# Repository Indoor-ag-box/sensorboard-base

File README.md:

[Indoor Agriculture Project](https://docs.google.com/document/d/1ArcZqPgIa82AwvjWtvZ9FeCffs26SfxBspnVomPGeAw/edit#)

## Sensorboard

The Sensorboard is based off of the [Arduino Nano](https://store.arduino.cc/usa/arduino-nano). It has a very minimal UI to:

* Enable and disable sensors on the board

* Select the ID number for the board

* Display current sensor readings

* Calibrate sensors (Calibration factors are stored in EEPROM)

The UI is based on an:

* [8x2 Char LCD Module](https://www.digikey.com/product-detail/en/newhaven-display-intl/NHD-0208BZ-FL-YBW/NHD-0208BZ-FL-YBW-ND/1701135)

* 3 Pushbuttons

The sensorboard reports all RAW values back to the pi. These may be filtered and averaged etc, but conversion from VOLTAGE to the actual data is handled by the pi.

The connections are as follows:

### Arduino Pins

<table>
  <tr>
    <td>Pin Name</td>
    <td>Pin Function</td>
    <td>Short Name</td>
    <td>Location</td>
  </tr>
  <tr>
    <td>D2 (INT)</td>
    <td>Misc Digital Input</td>
    <td>EMDI0</td>
    <td>Screw Terminal</td>
  </tr>
  <tr>
    <td>D3
</td>
    <td>Shift Register Serial</td>
    <td>SREG_SER</td>
    <td>On Board
</td>
  </tr>
  <tr>
    <td>D4</td>
    <td>Shift Register SRCLK</td>
    <td>SREG_SRCLK</td>
    <td>On Board</td>
  </tr>
  <tr>
    <td>D5</td>
    <td>CO2 Sensor UART TX</td>
    <td>ECO2R</td>
    <td>Board Connector</td>
  </tr>
  <tr>
    <td>D6</td>
    <td>CO2 Sensor UART RX</td>
    <td>ECO2R</td>
    <td>Board Connector</td>
  </tr>
  <tr>
    <td>D7 (SDA)</td>
    <td>RGB Color Sensor I2C SDA</td>
    <td>ECSDA</td>
    <td>Board Connector</td>
  </tr>
  <tr>
    <td>D8 (SCL)</td>
    <td>RGB Color Sensor I2C SCL</td>
    <td>ECSCL</td>
    <td>Board Connector</td>
  </tr>
  <tr>
    <td>D9</td>
    <td>Load Sensor Data</td>
    <td>LSDAT</td>
    <td>On Board</td>
  </tr>
  <tr>
    <td>D10</td>
    <td>Load Sensor Clock</td>
    <td>LSCLK</td>
    <td>On Board</td>
  </tr>
  <tr>
    <td>D11 (PWM)</td>
    <td>LCD Backlight LED+</td>
    <td>OLED+</td>
    <td>On Board</td>
  </tr>
  <tr>
    <td>D12</td>
    <td>Shift Register RCLK</td>
    <td>SREG_RCLK</td>
    <td>On Board</td>
  </tr>
  <tr>
    <td>D13</td>
    <td>Voltage Divider Enable</td>
    <td>DIVEN</td>
    <td>On Board</td>
  </tr>
  <tr>
    <td>A0</td>
    <td>Mux Sig Pin</td>
    <td>MUX_SIG</td>
    <td>On Board</td>
  </tr>
  <tr>
    <td>A1</td>
    <td>Mux S0</td>
    <td>MUX_S0</td>
    <td>On Board</td>
  </tr>
  <tr>
    <td>A2</td>
    <td>Mux S1</td>
    <td>MUX_S1</td>
    <td>On Board</td>
  </tr>
  <tr>
    <td>A3</td>
    <td>Mux S2</td>
    <td>MUX_S2</td>
    <td>On Board</td>
  </tr>
  <tr>
    <td>A4</td>
    <td>Hardware I2C SDA (For External Comms)</td>
    <td>I2C_SDA</td>
    <td>Board Connector</td>
  </tr>
  <tr>
    <td>A5</td>
    <td>Hardware I2C SCL (For External Comms)</td>
    <td>I2C_SDL</td>
    <td>Board Connector</td>
  </tr>
  <tr>
    <td>A6</td>
    <td>Mux S3</td>
    <td>MUX_S3</td>
    <td>On Board</td>
  </tr>
  <tr>
    <td>A7</td>
    <td>Mux EN</td>
    <td>MUX_EN</td>
    <td>On Board</td>
  </tr>
</table>

### Multiplexer

<table>
  <tr>
    <td>Pin Name</td>
    <td>Pin Function</td>
    <td>Short Name</td>
    <td>Location</td>
  </tr>
  <tr>
    <td>I0</td>
    <td>External Temp Sensor 0</td>
    <td>ETMP0</td>
    <td>Screw Terminal</td>
  </tr>
  <tr>
    <td>I1</td>
    <td>External Temp Sensor 1</td>
    <td>ETMP1</td>
    <td>Screw Terminal</td>
  </tr>
  <tr>
    <td>I2</td>
    <td>External Temp Sensor 2</td>
    <td>ETMP2</td>
    <td>Screw Terminal</td>
  </tr>
  <tr>
    <td>I3</td>
    <td>Soil Moisture Sensor 1 </td>
    <td>ESMT0</td>
    <td>Screw Terminal</td>
  </tr>
  <tr>
    <td>I4</td>
    <td>Soil Moisture Sensor 2</td>
    <td>ESMT0</td>
    <td>Screw Terminal</td>
  </tr>
  <tr>
    <td>I5</td>
    <td>Onboard Temp Sensor 0</td>
    <td>OTMP0</td>
    <td>On Board</td>
  </tr>
  <tr>
    <td>I6</td>
    <td>Onboard LDR 0</td>
    <td>OLDR0</td>
    <td>Board Connector</td>
  </tr>
  <tr>
    <td>I7</td>
    <td>O2 Sensor</td>
    <td>BO2G0</td>
    <td>On Board</td>
  </tr>
  <tr>
    <td>I8</td>
    <td>Ambient Humidity</td>
    <td>OMST0</td>
    <td>On board</td>
  </tr>
  <tr>
    <td>I9</td>
    <td>External Turbidity 0</td>
    <td>ETRB0</td>
    <td>Board Connector</td>
  </tr>
  <tr>
    <td>I10</td>
    <td></td>
    <td></td>
    <td></td>
  </tr>
  <tr>
    <td>I11</td>
    <td></td>
    <td></td>
    <td></td>
  </tr>
  <tr>
    <td>I12</td>
    <td>External Board Detection</td>
    <td>EEBD0</td>
    <td>Board Connector</td>
  </tr>
  <tr>
    <td>I13</td>
    <td>UI Button 1 (<)</td>
    <td>OUI0</td>
    <td>On Board</td>
  </tr>
  <tr>
    <td>I14</td>
    <td>UI Button 2 (*)</td>
    <td>OUI1</td>
    <td>On Board</td>
  </tr>
  <tr>
    <td>I15</td>
    <td>UI Button 3 (>)</td>
    <td>OUI2</td>
    <td>On Board</td>
  </tr>
</table>

A sensor board that we can stick all over the cabinet to sense critical environmental data. There will be more than one of these boards through the whole design. Sensor boards are based around the arduino mini which communicates with the Raspberry Pi as a master and the arduino responds as a [slave](https://www.arduino.cc/en/Tutorial/MasterWriter). 

Should be able to detect following variables (sensors are linked as hyperlinks):

* [Onboard temperature](https://www.digikey.com/product-detail/en/ametherm/1DC103K-EC/570-1229-ND/5970118)

* [External temperature (optional through some kind of screw terminal)](https://www.adafruit.com/product/372)

* [Ambient light Level](https://www.digikey.com/products/en?dc=16426)

* [Light Color](https://www.adafruit.com/product/1334?gclid=Cj0KCQiA2Y_UBRCGARIsALglqQ1tPgwjs8Q0iPb3CzkeynlRJk4hzR49dijqtHjcTRZPo-LJaD_BfX8aAv9AEALw_wcB)

* [Ambient Moisture](https://www.digikey.com/product-detail/en/honeywell-sensing-and-productivity-solutions/HIH-4030-003/480-3167-ND/1886072)

* [Soil Moisture (external)](https://www.sparkfun.com/products/13322)

* [O2 Content](https://www.seeedstudio.com/Grove-Oxygen-Sensor%28ME2-O2-%D0%A420%29-p-1541.html)

* [CO2 Content](https://www.ebay.com/itm/New-MH-Z19B-Infrared-Carbon-Dioxide-CO2-Monitor-Sensor-Module-UART-PWM-Output/302501791946?epid=5002546034&hash=item466e8308ca:g:nwoAAOSwH-dZ8ae~:sc:USPSFirstClass!02169!US!-1)

* [Reservoir Water Turgidity](https://www.dfrobot.com/product-1394.html)

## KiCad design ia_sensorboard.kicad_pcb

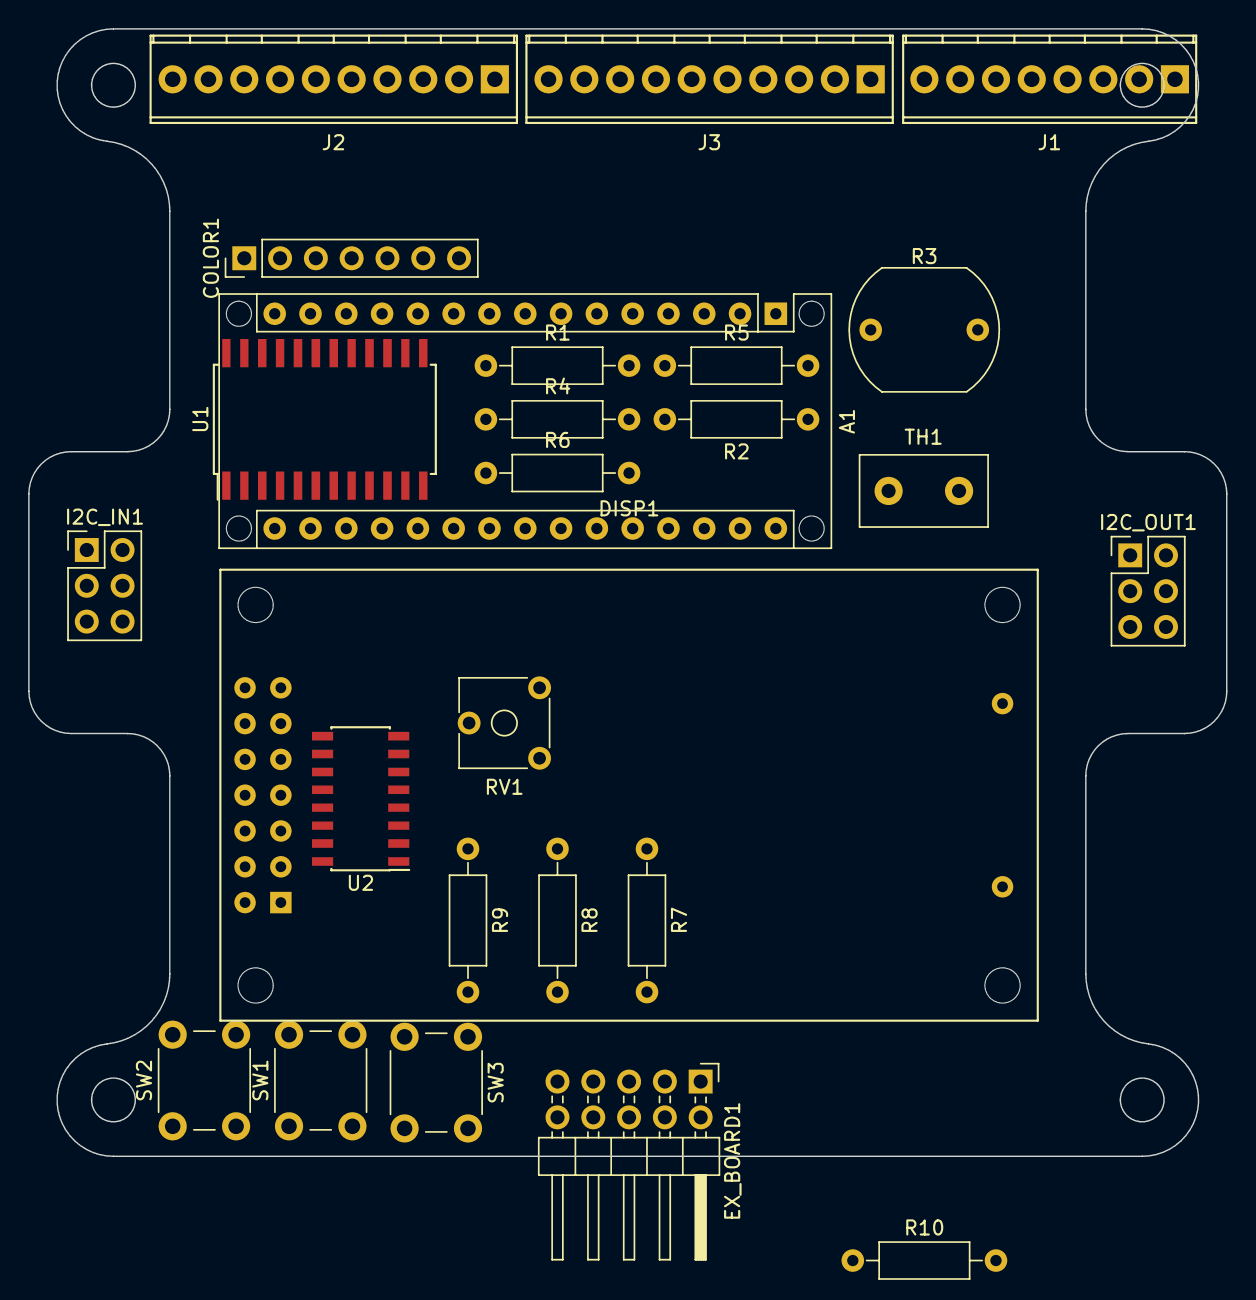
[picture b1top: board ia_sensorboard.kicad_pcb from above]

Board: 2 copper layers, 85.0 x 80.0 mm, 26 parts (0 on the bottom side), 36 nets, no tracks yet.

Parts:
A1: Arduino_Nano_v3.x; Arduino_Nano_WithMountingHoles
COLOR1: Conn_01x07_Female; Pin_Header_Straight_1x07_Pitch2.54mm
DISP1: LCD_ST7066_HD44880; NHD-0208BZ-RN-YBW-33V
EX_BOARD1: Conn_02x05_Odd_Even; Pin_Header_Angled_2x05_Pitch2.54mm
I2C_IN1, I2C_OUT1: Conn_02x03_Odd_Even; Pin_Header_Straight_2x03_Pitch2.54mm
J1: Screw_Terminal_01x08; TerminalBlock_Phoenix_MPT-2.54mm_8pol
J2, J3: Screw_Terminal_01x10; TerminalBlock_Phoenix_MPT-2.54mm_10pol
R1, R2, R5, R6, R7, R8, R9, R10: 10K; R_Axial_DIN0207_L6.3mm_D2.5mm_P10.16mm_Horizontal
R3: 10K; Resistor_LDR_10x8.5_RM7.6
R4: LDR03; R_Axial_DIN0207_L6.3mm_D2.5mm_P10.16mm_Horizontal
RV1: POT; Potentiometer_Trimmer_ACP_CA6v_Horizontal
SW1, SW2, SW3: SW_Push; SW_PUSH_6mm
TH1: 10K Thermistor; C_Disc_D9.0mm_W5.0mm_P5.00mm
U1: CD74HC4067; SOIC-24W_7.5x15.4mm_Pitch1.27mm
U2: 74HC595; SOIC-16_3.9x9.9mm_Pitch1.27mm

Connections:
+5V: A1.27, DISP1.2, EX_BOARD1.1, I2C_IN1.1, I2C_OUT1.1, J2.8, J3.1, R3.2, RV1.1, SW1.1, SW2.1, SW3.1, U1.24, U2.16
/ESMT0: J2.9, U1.5
/ESMT1: J3.2, U1.6
/ETMP0: J3.9, R5.1, U1.9
/ETMP1: J3.7, R6.1, U1.8
/ETMP2: J3.5, R7.1, U1.7
/OUI0: R8.2, SW1.2, U1.18
/OUI1: R9.2, SW2.2, U1.17
/OUI3: R10.2, SW3.2, U1.16
BO2G0: EX_BOARD1.4, U1.1
DIV_EN_PIN: A1.16, R2.2, R5.2, R6.2, R7.2
ECO2R: A1.9, EX_BOARD1.3
ECO2T: A1.8, EX_BOARD1.2
EMDI0: A1.5, J2.5
EMDI1: A1.6, J2.6
ERST0: A1.28, I2C_IN1.5, I2C_OUT1.5
ETRB0: EX_BOARD1.7, U1.22
GND: DISP1.1, DISP1.5, EX_BOARD1.10, I2C_IN1.6, I2C_OUT1.6, J2.7, J2.10, J3.3, J3.4, J3.6, J3.8, J3.10, R1.1, R4.2, R8.1, R9.1, R10.1, RV1.3, TH1.2, U1.12, U2.8
I2C_SCL: A1.25, I2C_IN1.4, I2C_OUT1.4
I2C_SDA: A1.24, I2C_IN1.3, I2C_OUT1.3
MUX_EN: A1.26, U1.15
MUX_S0: A1.20, U1.10
MUX_S1: A1.21, U1.11
MUX_S2: A1.22, U1.14
MUX_S3: A1.23, U1.13
MUX_SIG: A1.19, U1.2
unnamed: DISP1.3, RV1.2
unnamed: DISP1.4, U2.15
unnamed: DISP1.6, U2.1
unnamed: DISP1.11, U2.4
unnamed: DISP1.12, U2.5
unnamed: DISP1.13, U2.6
unnamed: DISP1.14, U2.7
OEBD0: EX_BOARD1.9, R1.2, U1.19
OLDR0: R3.1, R4.1, U1.3
OTMP0: R2.1, TH1.1, U1.4

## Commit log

2018-03-03 init
2018-03-03 adding readme
